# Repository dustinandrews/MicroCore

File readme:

Wiring diagrams, board designs and code to create an 8 input/8 output board that can be programmed from the arduino enviroment based off an Attiny13 chip.

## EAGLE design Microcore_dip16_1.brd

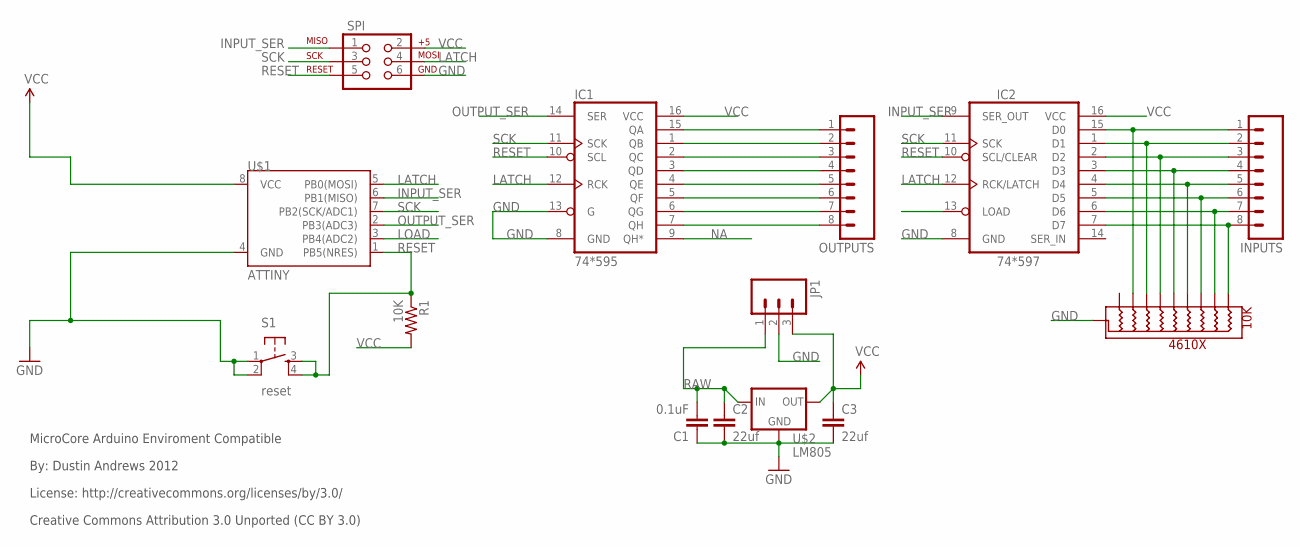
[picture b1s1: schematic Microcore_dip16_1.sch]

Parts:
10K: 4610X; 10-SIP
C1: 0.1uF; CAP-PTH-SMALL
C2, C3: 22uf; CAP-PTH-SMALL
IC1: 74*595; DIL16
IC2: 74*597; DIL16
INPUTS: M08LONGPADS; 1X08_LONGPADS
JP1: M03PTH; 1X03
OUTPUTS: M08LONGPADS; 1X08_LONGPADS
R1: 10K; AXIAL-0.4
S1: reset; TACTILE-PTH
SPI: AVR_SPI_PRG_6NS; 2X3-NS
U$1: ATTINY; DIP08
U$2: LM805; TO220-IGO

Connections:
GND: 10K.P$1 (GND), C1.1, C2.2, C3.2, IC1.8 (GND), IC1.13 (G), IC2.8 (GND), JP1.2, S1.1, S1.2, SPI.6, U$1.4 (GND), U$2.GND
INPUT_SER: IC2.9 (SER_OUT), SPI.1, U$1.6 (PB1(MISO))
LATCH: IC1.12 (RCK), IC2.12 (RCK/LATCH), SPI.4, U$1.5 (PB0(MOSI))
LOAD: IC2.13 (LOAD), U$1.3 (PB4(ADC2))
unnamed: IC1.15 (QA), OUTPUTS.1
unnamed: IC1.1 (QB), OUTPUTS.2
unnamed: IC1.2 (QC), OUTPUTS.3
unnamed: IC1.3 (QD), OUTPUTS.4
unnamed: IC1.4 (QE), OUTPUTS.5
unnamed: IC1.5 (QF), OUTPUTS.6
unnamed: IC1.6 (QG), OUTPUTS.7
unnamed: IC1.7 (QH), OUTPUTS.8
unnamed: 10K.P$3 (2), IC2.15 (D0), INPUTS.1
unnamed: 10K.P$4 (3), IC2.1 (D1), INPUTS.2
unnamed: 10K.P$5 (4), IC2.2 (D2), INPUTS.3
unnamed: 10K.P$6 (5), IC2.3 (D3), INPUTS.4
unnamed: 10K.P$7 (6), IC2.4 (D4), INPUTS.5
unnamed: 10K.P$8 (7), IC2.5 (D5), INPUTS.6
unnamed: 10K.P$9 (8), IC2.6 (D6), INPUTS.7
unnamed: 10K.P$10 (9), IC2.7 (D7), INPUTS.8
NA: IC1.9 (QH*)
OUTPUT_SER: IC1.14 (SER), U$1.2 (PB3(ADC3))
RAW: C1.2, C2.1, JP1.1, U$2.IN
RESET: IC1.10 (SCL), IC2.10 (SCL/CLEAR), R1.P$1 (1), S1.3, S1.4, SPI.5, U$1.1 (PB5(NRES))
SCK: IC1.11 (SCK), IC2.11 (SCK), SPI.3, U$1.7 (PB2(SCK/ADC1))
VCC: C3.1, IC1.16 (VCC), IC2.16 (VCC), JP1.3, R1.P$2 (2), SPI.2, U$1.8 (VCC), U$2.OUT

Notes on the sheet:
MicroCore Arduino Enviroment Compatible
By: Dustin Andrews 2012
License: http://creativecommons.org/licenses/by/3.0/
Creative Commons Attribution 3.0 Unported (CC BY 3.0)

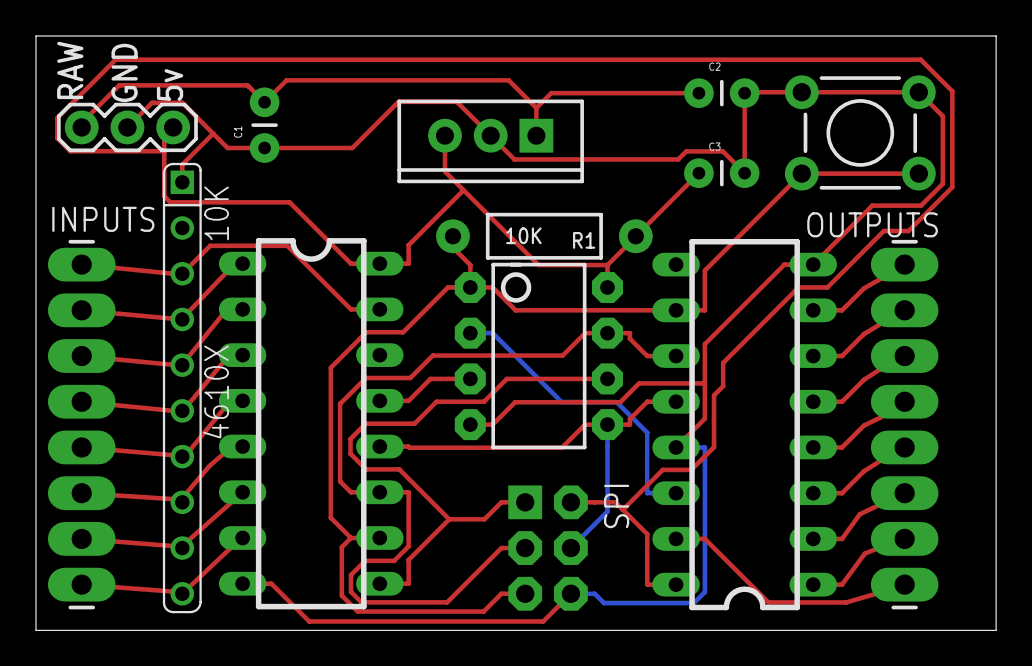
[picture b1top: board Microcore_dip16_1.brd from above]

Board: 2 copper layers, 53.3 x 33.0 mm, 14 parts (0 on the bottom side), 25 nets.

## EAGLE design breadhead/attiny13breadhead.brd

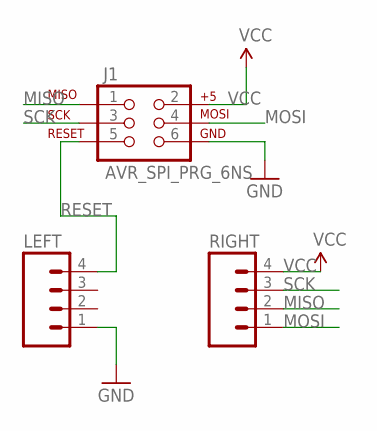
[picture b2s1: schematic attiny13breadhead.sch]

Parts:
J1: AVR_SPI_PRG_6NS; 2X3-NS
LEFT: M04PTH; 1X04
RIGHT: M04PTH; 1X04

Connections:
GND: J1.6, LEFT.1
MISO: J1.1, RIGHT.2
MOSI: J1.4, RIGHT.1
RESET: J1.5, LEFT.4
SCK: J1.3, RIGHT.3
VCC: J1.2, RIGHT.4

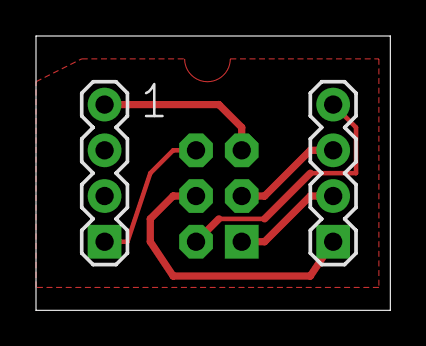
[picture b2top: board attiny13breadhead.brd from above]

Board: 2 copper layers, 19.7 x 15.2 mm, 3 parts (0 on the bottom side), 6 nets.

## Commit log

2012-03-25 Added Arduino code
2012-03-27 Added breadhead for attiny
2012-03-30 Added resistor array and power regulator

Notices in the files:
parts and their libraries:
SparkFun: Licensing: CC v3.0 Share-Alike You are welcome to use this library for commercial purposes.
